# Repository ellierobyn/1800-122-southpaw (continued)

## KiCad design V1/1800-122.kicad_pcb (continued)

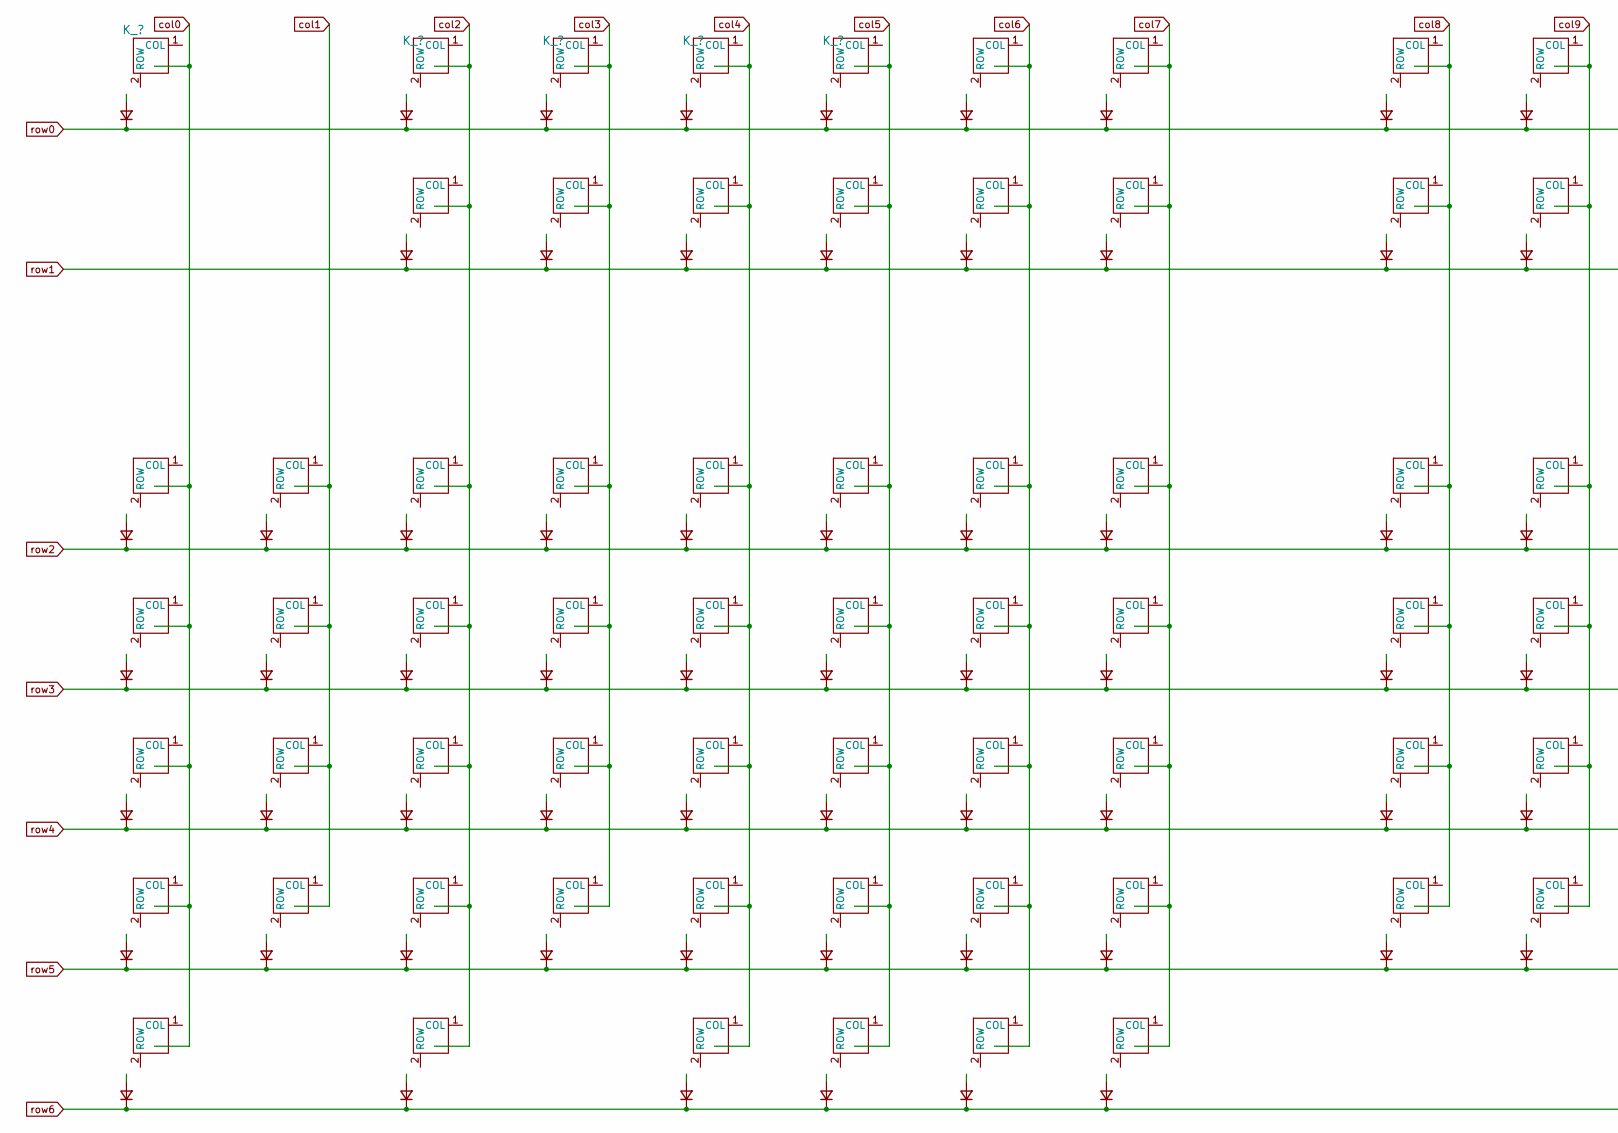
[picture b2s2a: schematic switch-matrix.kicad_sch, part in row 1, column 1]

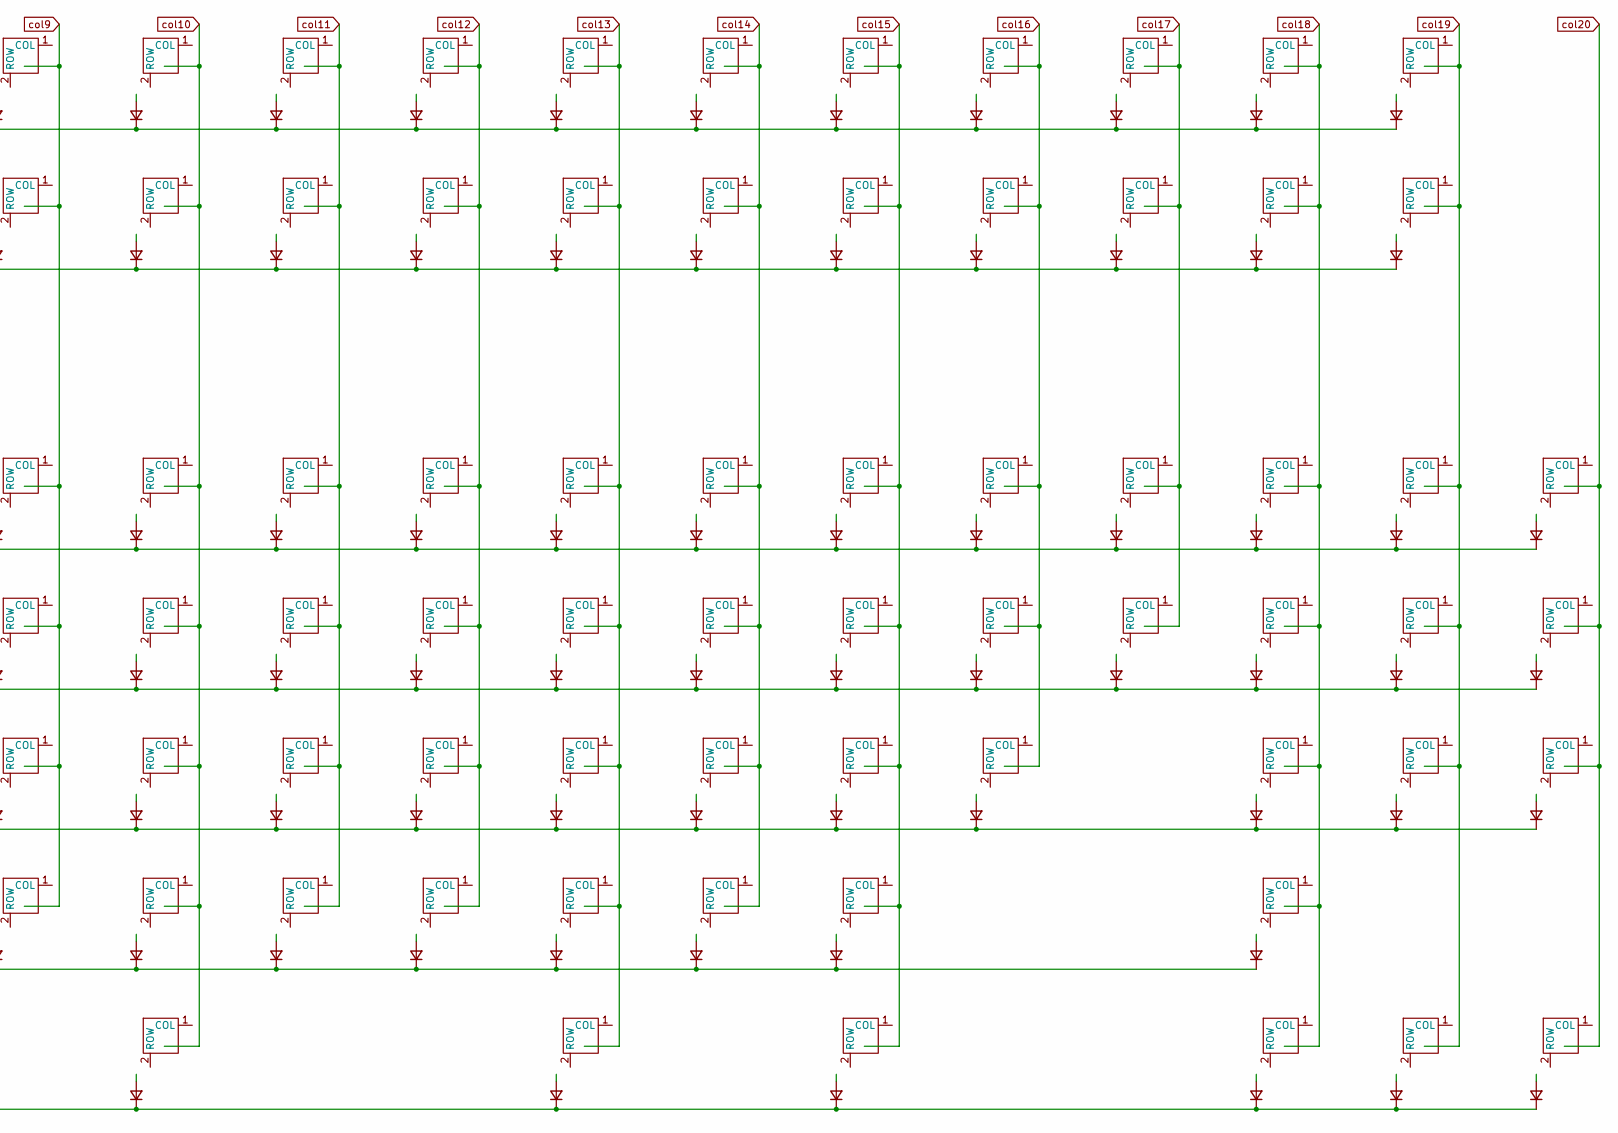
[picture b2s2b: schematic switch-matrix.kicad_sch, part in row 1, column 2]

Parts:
D1, D2, D3, D4, D5, D6, D7, D8, D9, D10, D11, D12, D13, D14, D15, D16, D17, D18, D19, D20, D21, D22, D23, D24, D25, D26, D27, D28, D29, D30, D31, D32, D33, D34, D35, D36, D37, D38, D39, D40, D41, D42, D43, D44, D45, D46, D47, D48, D49, D50, D51, D52, D53, D54, D55, D56, D57, D58, D59, D60, D61, D62, D63, D64, D65, D66, D67, D68, D69, D70, D71, D72, D73, D74, D75, D76, D77, D78, D79, D80, D81, D82, D83, D84, D85, D86, D87, D88, D89, D90, D91, D92, D93, D94, D95, D96, D97, D98, D99, D100, D101, D102, D103, D104, D105, D106, D107, D108, D109, D110, D111, D112, D113, D114, D115, D116, D117, D118, D119, D120, D121, D122, D123, D124, D125, D126, D127, D128: D; D_SOD-123
MX1, MX2, MX3, MX4, MX5, MX6, MX7, MX8, MX9, MX10, MX11, MX12, MX13, MX14, MX15, MX16, MX17, MX18, MX19, MX20, MX21, MX22, MX23, MX24, MX25, MX26, MX27, MX28, MX29, MX30, MX31, MX32, MX33, MX34, MX35, MX36, MX37, MX38, MX39, MX40, MX41, MX42, MX43, MX44, MX45, MX46, MX47, MX48, MX49, MX50, MX51, MX52, MX53, MX54, MX55, MX56, MX57, MX58, MX59, MX60, MX61, MX62, MX63, MX64, MX65, MX66, MX67, MX68, MX69, MX70, MX71, MX72, MX73, MX74, MX75, MX76, MX77, MX78, MX79, MX80, MX81, MX82, MX83, MX84, MX85, MX86, MX87, MX88, MX89, MX90, MX91, MX92, MX93, MX94, MX95, MX96, MX97, MX98, MX99, MX100, MX101, MX102, MX103, MX104, MX105, MX106, MX107, MX108, MX109, MX110, MX111, MX112, MX113, MX114, MX115, MX116, MX117, MX118, MX119, MX120, MX121, MX122, MX123, MX124, MX125, MX126, MX127, MX128: KEYSW; SW_Hotswap_Kailh_MX_1.00u

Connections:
unnamed: D1.2 (A), MX1.2 (ROW)
unnamed: D2.2 (A), MX2.2 (ROW)
unnamed: D3.2 (A), MX3.2 (ROW)
unnamed: D4.2 (A), MX4.2 (ROW)
unnamed: D5.2 (A), MX5.2 (ROW)
unnamed: D6.2 (A), MX6.2 (ROW)
unnamed: D7.2 (A), MX7.2 (ROW)
unnamed: D8.2 (A), MX8.2 (ROW)
unnamed: D9.2 (A), MX9.2 (ROW)
unnamed: D10.2 (A), MX10.2 (ROW)
unnamed: D11.2 (A), MX11.2 (ROW)
unnamed: D12.2 (A), MX12.2 (ROW)
unnamed: D13.2 (A), MX13.2 (ROW)
unnamed: D14.2 (A), MX14.2 (ROW)
unnamed: D15.2 (A), MX15.2 (ROW)
unnamed: D16.2 (A), MX16.2 (ROW)
unnamed: D17.2 (A), MX17.2 (ROW)
unnamed: D18.2 (A), MX18.2 (ROW)
unnamed: D19.2 (A), MX19.2 (ROW)
unnamed: D20.2 (A), MX20.2 (ROW)
unnamed: D21.2 (A), MX21.2 (ROW)
unnamed: D22.2 (A), MX22.2 (ROW)
unnamed: D23.2 (A), MX23.2 (ROW)
unnamed: D24.2 (A), MX24.2 (ROW)
unnamed: D25.2 (A), MX25.2 (ROW)
unnamed: D26.2 (A), MX26.2 (ROW)
unnamed: D27.2 (A), MX27.2 (ROW)
unnamed: D28.2 (A), MX28.2 (ROW)
unnamed: D29.2 (A), MX29.2 (ROW)
unnamed: D30.2 (A), MX30.2 (ROW)
unnamed: D31.2 (A), MX31.2 (ROW)
unnamed: D32.2 (A), MX32.2 (ROW)
unnamed: D33.2 (A), MX33.2 (ROW)
unnamed: D34.2 (A), MX34.2 (ROW)
unnamed: D35.2 (A), MX35.2 (ROW)
unnamed: D36.2 (A), MX36.2 (ROW)
unnamed: D37.2 (A), MX37.2 (ROW)
unnamed: D38.2 (A), MX38.2 (ROW)
unnamed: D39.2 (A), MX39.2 (ROW)
unnamed: D40.2 (A), MX40.2 (ROW)
unnamed: D41.2 (A), MX41.2 (ROW)
unnamed: D42.2 (A), MX42.2 (ROW)
unnamed: D43.2 (A), MX43.2 (ROW)
unnamed: D44.2 (A), MX44.2 (ROW)
unnamed: D45.2 (A), MX45.2 (ROW)
unnamed: D46.2 (A), MX46.2 (ROW)
unnamed: D47.2 (A), MX47.2 (ROW)
unnamed: D48.2 (A), MX48.2 (ROW)
unnamed: D49.2 (A), MX49.2 (ROW)
unnamed: D50.2 (A), MX50.2 (ROW)
unnamed: D51.2 (A), MX51.2 (ROW)
unnamed: D52.2 (A), MX52.2 (ROW)
unnamed: D53.2 (A), MX53.2 (ROW)
unnamed: D54.2 (A), MX54.2 (ROW)
unnamed: D55.2 (A), MX55.2 (ROW)
unnamed: D56.2 (A), MX56.2 (ROW)
unnamed: D57.2 (A), MX57.2 (ROW)
unnamed: D58.2 (A), MX58.2 (ROW)
unnamed: D59.2 (A), MX59.2 (ROW)
unnamed: D60.2 (A), MX60.2 (ROW)
unnamed: D61.2 (A), MX61.2 (ROW)
unnamed: D62.2 (A), MX62.2 (ROW)
unnamed: D63.2 (A), MX63.2 (ROW)
unnamed: D64.2 (A), MX64.2 (ROW)
unnamed: D65.2 (A), MX65.2 (ROW)
unnamed: D66.2 (A), MX66.2 (ROW)
unnamed: D67.2 (A), MX67.2 (ROW)
unnamed: D68.2 (A), MX68.2 (ROW)
unnamed: D69.2 (A), MX69.2 (ROW)
unnamed: D70.2 (A), MX70.2 (ROW)
unnamed: D71.2 (A), MX71.2 (ROW)
unnamed: D72.2 (A), MX72.2 (ROW)
unnamed: D73.2 (A), MX73.2 (ROW)
unnamed: D74.2 (A), MX74.2 (ROW)
unnamed: D75.2 (A), MX75.2 (ROW)
unnamed: D76.2 (A), MX76.2 (ROW)
unnamed: D77.2 (A), MX77.2 (ROW)
unnamed: D78.2 (A), MX78.2 (ROW)
unnamed: D79.2 (A), MX79.2 (ROW)
unnamed: D80.2 (A), MX80.2 (ROW)
unnamed: D81.2 (A), MX81.2 (ROW)
unnamed: D82.2 (A), MX82.2 (ROW)
unnamed: D83.2 (A), MX83.2 (ROW)
unnamed: D84.2 (A), MX84.2 (ROW)
unnamed: D85.2 (A), MX85.2 (ROW)
unnamed: D86.2 (A), MX86.2 (ROW)
unnamed: D87.2 (A), MX87.2 (ROW)
unnamed: D88.2 (A), MX88.2 (ROW)
unnamed: D89.2 (A), MX89.2 (ROW)
unnamed: D90.2 (A), MX90.2 (ROW)
unnamed: D91.2 (A), MX91.2 (ROW)
unnamed: D92.2 (A), MX92.2 (ROW)
unnamed: D93.2 (A), MX93.2 (ROW)
unnamed: D94.2 (A), MX94.2 (ROW)
unnamed: D95.2 (A), MX95.2 (ROW)
unnamed: D96.2 (A), MX96.2 (ROW)
unnamed: D97.2 (A), MX97.2 (ROW)
unnamed: D98.2 (A), MX98.2 (ROW)
unnamed: D99.2 (A), MX99.2 (ROW)
unnamed: D100.2 (A), MX100.2 (ROW)
unnamed: D101.2 (A), MX101.2 (ROW)
unnamed: D102.2 (A), MX102.2 (ROW)
unnamed: D103.2 (A), MX103.2 (ROW)
unnamed: D104.2 (A), MX104.2 (ROW)
unnamed: D105.2 (A), MX105.2 (ROW)
unnamed: D106.2 (A), MX106.2 (ROW)
unnamed: D107.2 (A), MX107.2 (ROW)
unnamed: D108.2 (A), MX108.2 (ROW)
unnamed: D109.2 (A), MX109.2 (ROW)
unnamed: D110.2 (A), MX110.2 (ROW)
unnamed: D111.2 (A), MX111.2 (ROW)
unnamed: D112.2 (A), MX112.2 (ROW)
unnamed: D113.2 (A), MX113.2 (ROW)
unnamed: D114.2 (A), MX114.2 (ROW)
unnamed: D115.2 (A), MX115.2 (ROW)
unnamed: D116.2 (A), MX116.2 (ROW)
unnamed: D117.2 (A), MX117.2 (ROW)
unnamed: D118.2 (A), MX118.2 (ROW)
unnamed: D119.2 (A), MX119.2 (ROW)
unnamed: D120.2 (A), MX120.2 (ROW)
unnamed: D121.2 (A), MX121.2 (ROW)
unnamed: D122.2 (A), MX122.2 (ROW)
unnamed: D123.2 (A), MX123.2 (ROW)
unnamed: D124.2 (A), MX124.2 (ROW)
unnamed: D125.2 (A), MX125.2 (ROW)
unnamed: D126.2 (A), MX126.2 (ROW)
unnamed: D127.2 (A), MX127.2 (ROW)
unnamed: D128.2 (A), MX128.2 (ROW)
col0: MX1.1 (COL), MX38.1 (COL), MX59.1 (COL), MX80.1 (COL), MX100.1 (COL), MX117.1 (COL); also elsewhere on the board
col1: MX39.1 (COL), MX60.1 (COL), MX81.1 (COL), MX101.1 (COL); also elsewhere on the board
col2: MX2.1 (COL), MX20.1 (COL), MX40.1 (COL), MX61.1 (COL), MX82.1 (COL), MX102.1 (COL), MX118.1 (COL); also elsewhere on the board
col3: MX3.1 (COL), MX21.1 (COL), MX41.1 (COL), MX62.1 (COL), MX83.1 (COL), MX103.1 (COL); also elsewhere on the board
col4: MX4.1 (COL), MX22.1 (COL), MX42.1 (COL), MX63.1 (COL), MX84.1 (COL), MX104.1 (COL), MX119.1 (COL); also elsewhere on the board
col5: MX5.1 (COL), MX23.1 (COL), MX43.1 (COL), MX64.1 (COL), MX85.1 (COL), MX105.1 (COL), MX120.1 (COL); also elsewhere on the board
col6: MX6.1 (COL), MX24.1 (COL), MX44.1 (COL), MX65.1 (COL), MX86.1 (COL), MX106.1 (COL), MX121.1 (COL); also elsewhere on the board
col7: MX7.1 (COL), MX25.1 (COL), MX45.1 (COL), MX66.1 (COL), MX87.1 (COL), MX107.1 (COL), MX122.1 (COL); also elsewhere on the board
col8: MX8.1 (COL), MX26.1 (COL), MX46.1 (COL), MX67.1 (COL), MX88.1 (COL), MX108.1 (COL); also elsewhere on the board
col9: MX9.1 (COL), MX27.1 (COL), MX47.1 (COL), MX68.1 (COL), MX89.1 (COL), MX109.1 (COL); also elsewhere on the board
col10: MX10.1 (COL), MX28.1 (COL), MX48.1 (COL), MX69.1 (COL), MX90.1 (COL), MX110.1 (COL), MX123.1 (COL); also elsewhere on the board
col11: MX11.1 (COL), MX29.1 (COL), MX49.1 (COL), MX70.1 (COL), MX91.1 (COL), MX111.1 (COL); also elsewhere on the board
col12: MX12.1 (COL), MX30.1 (COL), MX50.1 (COL), MX71.1 (COL), MX92.1 (COL), MX112.1 (COL); also elsewhere on the board
col13: MX13.1 (COL), MX31.1 (COL), MX51.1 (COL), MX72.1 (COL), MX93.1 (COL), MX113.1 (COL), MX124.1 (COL); also elsewhere on the board
col14: MX14.1 (COL), MX32.1 (COL), MX52.1 (COL), MX73.1 (COL), MX94.1 (COL), MX114.1 (COL); also elsewhere on the board
col15: MX15.1 (COL), MX33.1 (COL), MX53.1 (COL), MX74.1 (COL), MX95.1 (COL), MX115.1 (COL), MX125.1 (COL); also elsewhere on the board
col16: MX16.1 (COL), MX34.1 (COL), MX54.1 (COL), MX75.1 (COL), MX96.1 (COL); also elsewhere on the board
col17: MX17.1 (COL), MX35.1 (COL), MX55.1 (COL), MX76.1 (COL); also elsewhere on the board
col18: MX18.1 (COL), MX36.1 (COL), MX56.1 (COL), MX77.1 (COL), MX97.1 (COL), MX116.1 (COL), MX126.1 (COL); also elsewhere on the board
col19: MX19.1 (COL), MX37.1 (COL), MX57.1 (COL), MX78.1 (COL), MX98.1 (COL), MX127.1 (COL); also elsewhere on the board
col20: MX58.1 (COL), MX79.1 (COL), MX99.1 (COL), MX128.1 (COL); also elsewhere on the board
row0: D1.1 (K), D2.1 (K), D3.1 (K), D4.1 (K), D5.1 (K), D6.1 (K), D7.1 (K), D8.1 (K), D9.1 (K), D10.1 (K), D11.1 (K), D12.1 (K), D13.1 (K), D14.1 (K), D15.1 (K), D16.1 (K), D17.1 (K), D18.1 (K), D19.1 (K); also elsewhere on the board
row1: D20.1 (K), D21.1 (K), D22.1 (K), D23.1 (K), D24.1 (K), D25.1 (K), D26.1 (K), D27.1 (K), D28.1 (K), D29.1 (K), D30.1 (K), D31.1 (K), D32.1 (K), D33.1 (K), D34.1 (K), D35.1 (K), D36.1 (K), D37.1 (K); also elsewhere on the board
row2: D38.1 (K), D39.1 (K), D40.1 (K), D41.1 (K), D42.1 (K), D43.1 (K), D44.1 (K), D45.1 (K), D46.1 (K), D47.1 (K), D48.1 (K), D49.1 (K), D50.1 (K), D51.1 (K), D52.1 (K), D53.1 (K), D54.1 (K), D55.1 (K), D56.1 (K), D57.1 (K), D58.1 (K); also elsewhere on the board
row3: D59.1 (K), D60.1 (K), D61.1 (K), D62.1 (K), D63.1 (K), D64.1 (K), D65.1 (K), D66.1 (K), D67.1 (K), D68.1 (K), D69.1 (K), D70.1 (K), D71.1 (K), D72.1 (K), D73.1 (K), D74.1 (K), D75.1 (K), D76.1 (K), D77.1 (K), D78.1 (K), D79.1 (K); also elsewhere on the board
row4: D80.1 (K), D81.1 (K), D82.1 (K), D83.1 (K), D84.1 (K), D85.1 (K), D86.1 (K), D87.1 (K), D88.1 (K), D89.1 (K), D90.1 (K), D91.1 (K), D92.1 (K), D93.1 (K), D94.1 (K), D95.1 (K), D96.1 (K), D97.1 (K), D98.1 (K), D99.1 (K); also elsewhere on the board
row5: D100.1 (K), D101.1 (K), D102.1 (K), D103.1 (K), D104.1 (K), D105.1 (K), D106.1 (K), D107.1 (K), D108.1 (K), D109.1 (K), D110.1 (K), D111.1 (K), D112.1 (K), D113.1 (K), D114.1 (K), D115.1 (K), D116.1 (K); also elsewhere on the board
row6: D117.1 (K), D118.1 (K), D119.1 (K), D120.1 (K), D121.1 (K), D122.1 (K), D123.1 (K), D124.1 (K), D125.1 (K), D126.1 (K), D127.1 (K), D128.1 (K); also elsewhere on the board

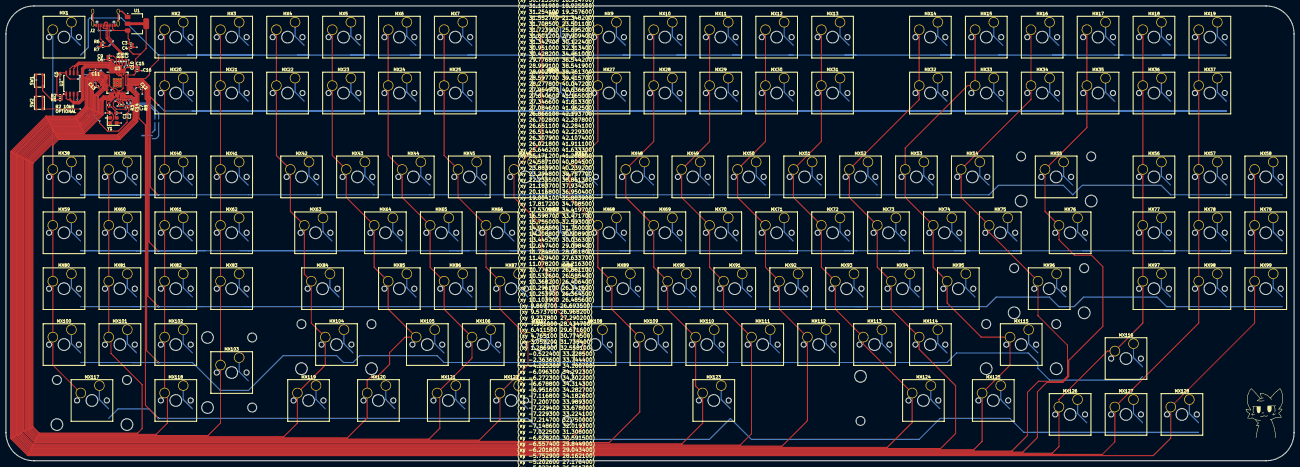
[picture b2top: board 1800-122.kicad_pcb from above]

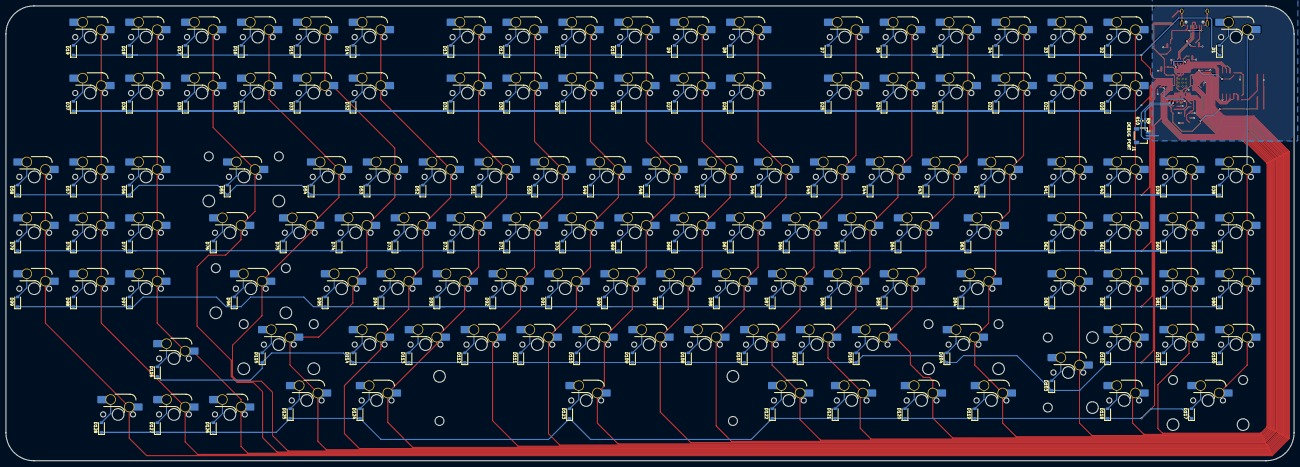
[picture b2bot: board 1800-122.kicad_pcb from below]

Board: 2 copper layers, 439.0 x 155.0 mm, 290 parts (131 on the bottom side), 181 nets.
